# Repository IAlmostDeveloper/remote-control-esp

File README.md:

# remote-control-esp

## Прошивка для контроллера в рамках проекта RemoteControl

#### Контроллер выполняет роль устройства, передающего получаемый сигнал приборам, управляемым с помощью инфракрасных ДУ пультов, что позволяет использовать его и приложение-клиент вместо оригинального пульта. 

#### Также контроллер имеет функцию приемника, позволяя добавлять в приложение-клиент кнопки оригинального пульта.

### Зависимости для сборки прошивки:
- ESP8266 (https://github.com/esp8266/Arduino)
- ArduinoJson 5
- IRRemoteESP8266
- PubSubClient

Все библиотеки устанавливаются через менеджер библиотек в Arduino IDE

### Инструкция по сборке:
- Собирать как проект в среде разработки Arduino IDE
- Необходимо установить утилиту ESP8266FS для записи файловой системы в контроллер, а затем загрузить файловую систему через Arduino IDE
- Как загрузить файловую систему в esp8266: http://digitrode.ru/computing-devices/mcu_cpu/2186-ustanavlivaem-zagruzchik-faylovoy-sistemy-esp8266-s-pomoschyu-arduino-ide.html 
### 
## Cхема устройства:

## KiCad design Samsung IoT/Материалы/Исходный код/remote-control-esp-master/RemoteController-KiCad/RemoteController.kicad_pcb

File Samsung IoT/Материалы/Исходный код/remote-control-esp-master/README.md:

# remote-control-esp

## Прошивка для контроллера в рамках проекта RemoteControl

#### Контроллер выполняет роль устройства, передающего получаемый сигнал приборам, управляемым с помощью инфракрасных ДУ пультов, что позволяет использовать его и приложение-клиент вместо оригинального пульта. 

#### Также контроллер имеет функцию приемника, позволяя добавлять в приложение-клиент кнопки оригинального пульта.

### Зависимости для сборки прошивки:
- ESP8266 (https://github.com/esp8266/Arduino)
- ArduinoJson 5
- IRRemoteESP8266
- PubSubClient

### Инструкция по сборке:
- Собирать как проект в среде разработки Arduino IDE

## Cхема устройства:

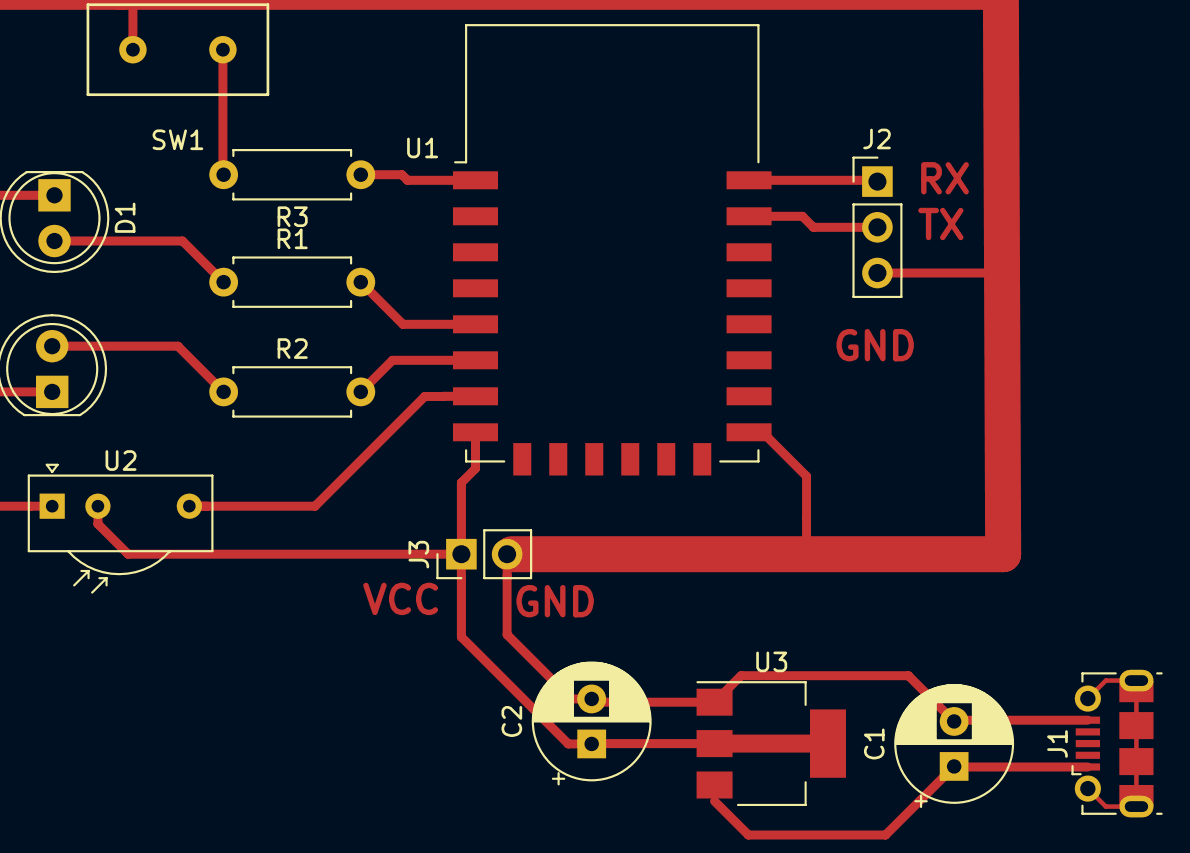
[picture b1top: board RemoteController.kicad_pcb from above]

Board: 2 copper layers, 14 parts (0 on the bottom side), 12 nets.

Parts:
C1, C2: 100mF; CP_Radial_D6.3mm_P2.50mm
D1: IR_LED; LED_D5.0mm
D2: LED; LED_D5.0mm
J1: USB_B_Micro; USB_Micro-B_Molex-105017-0001
J2: Conn_01x03; PinHeader_1x03_P2.54mm_Vertical
J3: ext.power; PinHeader_1x02_P2.54mm_Vertical
R1, R2: 220 Ohm; R_Axial_DIN0207_L6.3mm_D2.5mm_P7.62mm_Horizontal
R3: 12k; R_Axial_DIN0207_L6.3mm_D2.5mm_P7.62mm_Horizontal
SW1: SW_DPST_x2; Button Tactile 5 MM
U1: ESP-12E
U2: TSOP1738; Vishay_CAST-3Pin
U3: AMS1117-3.3; SOT-223-3_TabPin2

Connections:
GNDD: C1.2, C2.2, D1.1, D2.1, J1.5, J2.3, J3.2, SW1.1, U1.15, U2.1, U3.1
unnamed: C1.1, J1.1, U3.3
unnamed: C2.1, J3.1, U1.8, U2.2, U3.2
unnamed: D1.2, R1.1
unnamed: D2.2, R2.1
unnamed: J2.1, U1.22
unnamed: J2.2, U1.21
unnamed: R1.2, U1.5
unnamed: R2.2, U1.6
unnamed: R3.1, U1.1
unnamed: R3.2, SW1.2
unnamed: U1.7, U2.3

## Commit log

2020-05-21 sketch for IR controller
2020-05-25 some refactor
2020-06-04 ap settings pages
2020-06-04 split code into files
2020-06-05 small fix
2020-06-05 added styles
2020-06-06 soft and hard reset options
2020-06-06 ap mode fix
2020-06-17 code sending with delay
2020-06-27 added readme.md
2020-06-27 add schematic
2020-06-27 rm readme
2020-06-28 added KiCad files
2020-09-30 Все исходники лежат здесь
2020-10-09 fixed conflicts
2020-11-07 added alive signal
